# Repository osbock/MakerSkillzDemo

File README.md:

# MakerSkillzDemo
An object designed to exercise many of the tools at the Garden

## Arduino Code
The main program for this workshop is neopixel-webserver
### Setup
In Arduino set preferences to point the sketchbook folder to the arduino directory of this repo.
[Change Arduino Preferences](./assets/Arduino-prefs.png)

 * save and reopen arduino
 * open neopixel-webserver from the sketchbook menu
 * edit arduino_secrets.h (second tab)
  ** Change #define SECRET_SSID "" \\ put a unique name for your project in the quotes. This will make your project into a unique hotspot that you will connect to to control it, so choose a name others in the class are not likely to use.
 * connect your project via USB to the PC you are using to program it.
 * Tools/Board menu -- select "Adafruit Feather M0"
 * Tools/Port menu -- select the com port that your board is connected to. 
 * press the upload button (left pointing arrow next to the check mark at the top of the arduino window
 
### Connecting
 * from your phone or PC connect to the hotspot name you chose (SECRET_SSID). If your phone warns you that it doesn't have internet, connect anyway.
 * in a browser, type in http://192.168.1.1 (The http is important, as https is the default and we haven't set up the required certificates for that.

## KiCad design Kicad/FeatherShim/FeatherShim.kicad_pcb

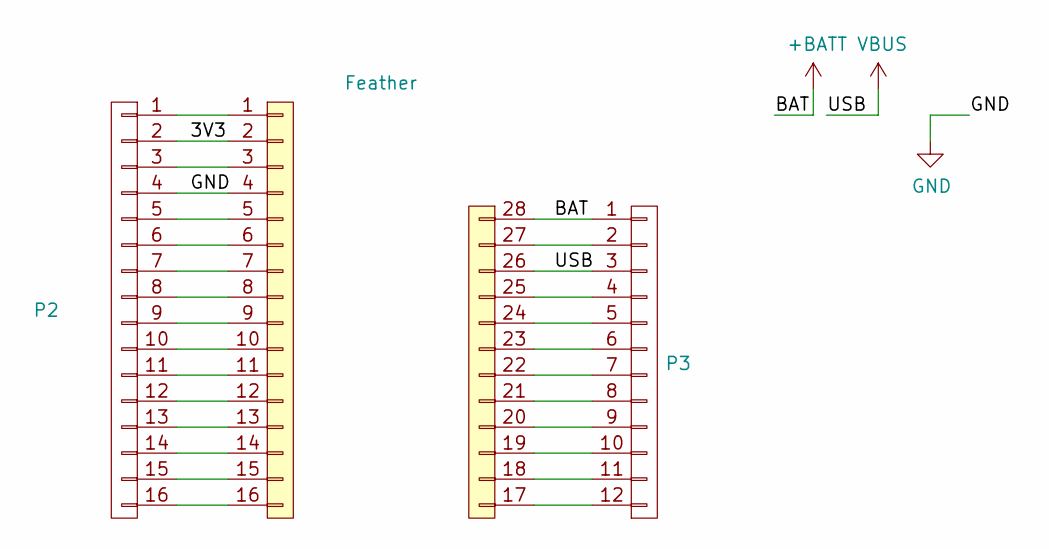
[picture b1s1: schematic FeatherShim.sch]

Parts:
P1: Feather; FEATHER_Common
P2: CONN_01X16; Pin_Header_Straight_1x16_Pitch2.54mm
P3: CONN_01X12; Pin_Header_Straight_1x12_Pitch2.54mm

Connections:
+BATT: P1.28, P3.1
/3V3: P1.2, P2.2
GND: P1.4, P2.4
unnamed: P1.1, P2.1
unnamed: P1.3, P2.3
unnamed: P1.5, P2.5
unnamed: P1.6, P2.6
unnamed: P1.7, P2.7
unnamed: P1.8, P2.8
unnamed: P1.9, P2.9
unnamed: P1.10, P2.10
unnamed: P1.11, P2.11
unnamed: P1.12, P2.12
unnamed: P1.13, P2.13
unnamed: P1.14, P2.14
unnamed: P1.15, P2.15
unnamed: P1.16, P2.16
unnamed: P1.17, P3.12
unnamed: P1.18, P3.11
unnamed: P1.19, P3.10
unnamed: P1.20, P3.9
unnamed: P1.21, P3.8
unnamed: P1.22, P3.7
unnamed: P1.23, P3.6
unnamed: P1.24, P3.5
unnamed: P1.25, P3.4
unnamed: P1.27, P3.2
VBUS: P1.26, P3.3

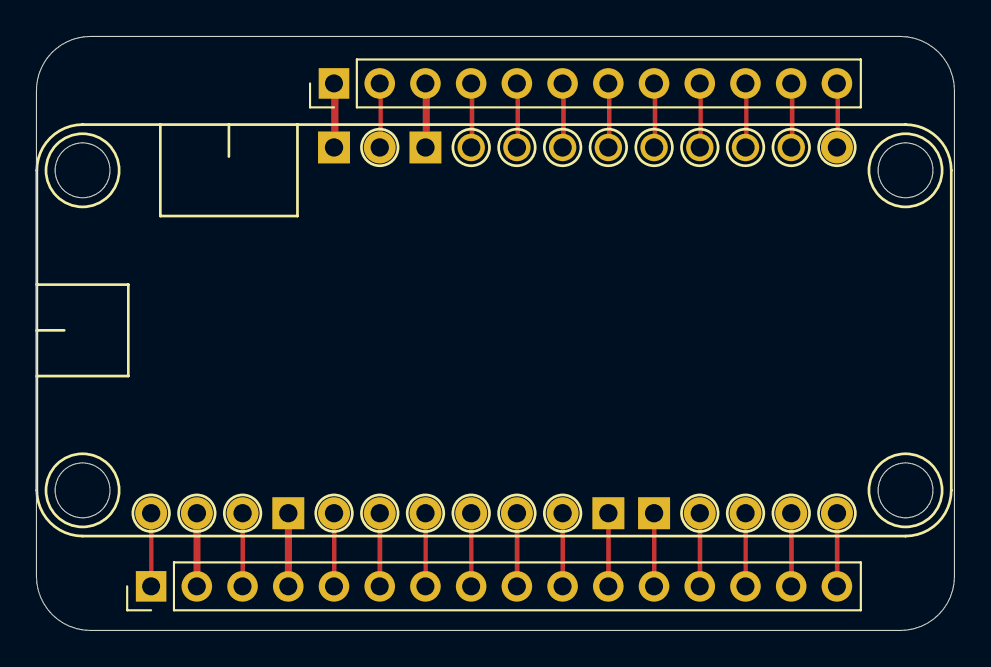
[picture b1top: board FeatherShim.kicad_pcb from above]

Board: 2 copper layers, 51.0 x 33.0 mm, 3 parts (0 on the bottom side), 28 nets.

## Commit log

2019-12-03 initial commit with arduino code and structure?
2019-12-04 add web buttons
2019-12-04 clean up led demo plus change button size on webserver
2019-12-04 temp. add of magneto grid
2019-12-05 remove magneto-grid, not part of this project
2019-12-12 initial arduino readme
2019-12-12 update pictures
2019-12-30 add shim board kicad files
2019-12-30 thicken power traces
